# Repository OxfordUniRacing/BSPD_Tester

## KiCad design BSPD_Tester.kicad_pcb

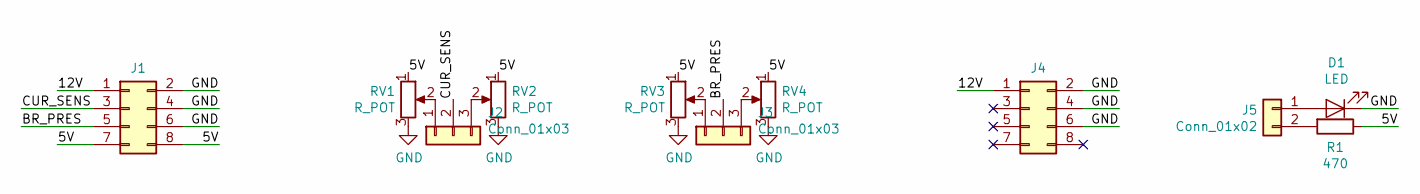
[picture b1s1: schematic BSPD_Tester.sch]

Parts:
D1: LED; LED_D3.0mm
J1, J4: Conn_02x04_Odd_Even; IDC-Header_2x04_P2.54mm_Vertical
J2, J3: Conn_01x03; PinHeader_1x03_P2.54mm_Vertical
J5: Conn_01x02; PinHeader_1x02_P2.54mm_Vertical
R1: 470; R_Axial_DIN0207_L6.3mm_D2.5mm_P10.16mm_Horizontal
RV1, RV2, RV3, RV4: R_POT; Potentiometer_Vishay_43_Horizontal

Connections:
/5V: J1.7, J1.8, R1.1, RV1.1, RV2.1, RV3.1, RV4.1
/12V: J1.1, J4.1
/BR_PRES: J1.5, J3.2
/CUR_SENS: J1.3, J2.2
GND: D1.1 (K), J1.2, J1.4, J1.6, J4.2, J4.4, J4.6, RV1.3, RV2.3, RV3.3, RV4.3
unnamed: D1.2 (A), J5.1
unnamed: J2.1, RV1.2
unnamed: J2.3, RV2.2
unnamed: J3.1, RV3.2
unnamed: J3.3, RV4.2
unnamed: J5.2, R1.2

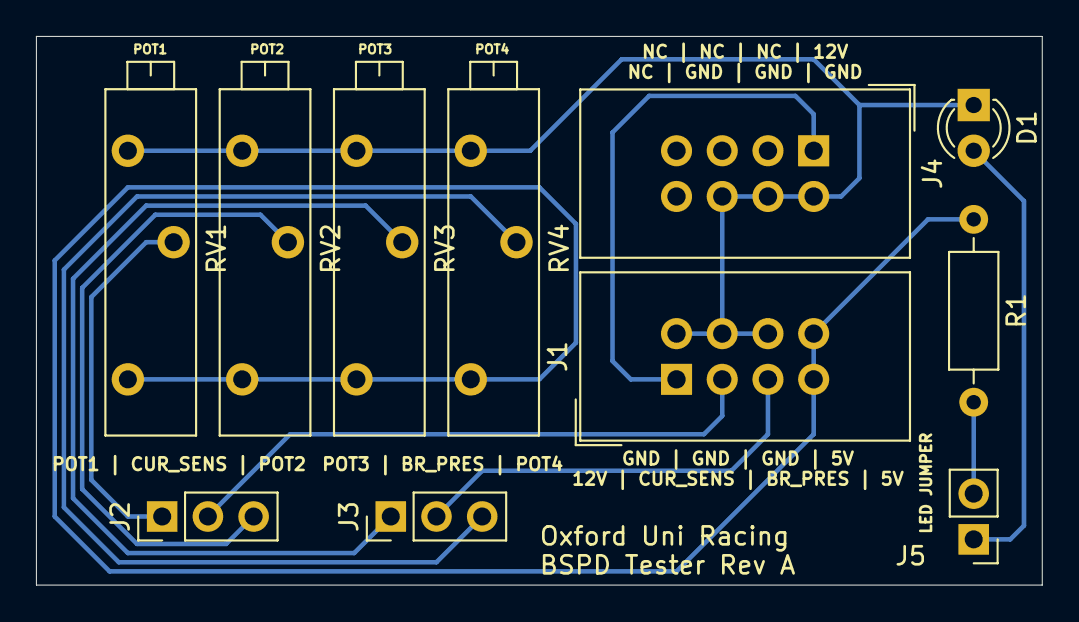
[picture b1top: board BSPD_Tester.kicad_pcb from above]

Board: 2 copper layers, 55.9 x 30.5 mm, 11 parts (0 on the bottom side), 11 nets.

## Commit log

2020-02-10 import
2021-11-17 Added better silkscreen for connectors
